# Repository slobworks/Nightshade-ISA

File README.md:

NIGHTSHADE v0.8c2 - Public Domain Cirrus Logic CL-GD542x Based ISA VGA Card

As it says on the package. This card supports a maximum memory size of 1MB or 2MB, depending on the chip you use, using traditional multiple-CAS FPM 256Kx16 SOJ memory. 70ns or faster is recommended.
Created using KiCAD 8.0.

Features:
- Four layer PCB with generous stitching vias for maximum possible signal integrity
- Optional dedicated regulator for analog DAC power for further improved picture quality
- Supports 1MB of memory with CL-GD5424, or 2MB with CL-GD5426/5428/5429
- Compatible with the N-well variants of the CL-GD542x, including the CL-GD5424, GD5426, GD5428 and GD5429
- Uses 29C010-compatible flash memory for reduced cost; has options to select one of four 32K banks within the large 128K flash memory if you wish to try multiple video BIOSes
- Features my own hand-drawn artwork on back of board

Release History:
- 0.8a: Fixed VESA Feature Connector pinout, now conforms to Cirrus datasheet
- 0.8b: Resolved a number of issues related to VGA output quality (no more wavy interference onscreen!), and reduced the parts count a bit. Fewer parts means less $$ spent, and less breathing of solder fumes.
- 0.8b2: Changed LM334SM to the _much_ cheaper LM334M.
- 0.8c: Pretty heavy tweak-up of both layout, ground pours, and placement of 75 ohm termination resistors following feedback from TmEE, Jorge and others. Thanks everyone who spoke up to help.
Also re-added DPAK LF50 regulator for the RAMDAC, and yes, it is optional if you want to pinch pennies on the dollar - just remember to only populate R22 if you're **not** using a regulator. If you're installing the regulator, leave R22 **OPEN**.
- 0.8c1: Changed ROM footprint to an SMD PLCC-32 socket, and had to re-space stuff around it to make it fit. This looks like it ought to work: https://www.digikey.com/en/products/detail/amphenol-cs-fci/69802-132LF/2023294
- 0.8c2: Moved the LDO and related junk to the front of the board to help minimize the potential for damage. Hopefully things don't get too hot, where it is.

Other people's stuff I've used:
- PLCC-32 footprint from KiCAD (SchrodingersGat ?): https://github.com/KiCad/Housings_LCC.pretty/blob/master/PLCC-32_SMD-Socket.kicad_mod

Released into the Public Domain. Use whatever license floats your boat on your own edits.

As you can see I'm a bit of a neophyte when it comes to this GitHub stuff.
Expect this to change as I become more familiar with the platform.

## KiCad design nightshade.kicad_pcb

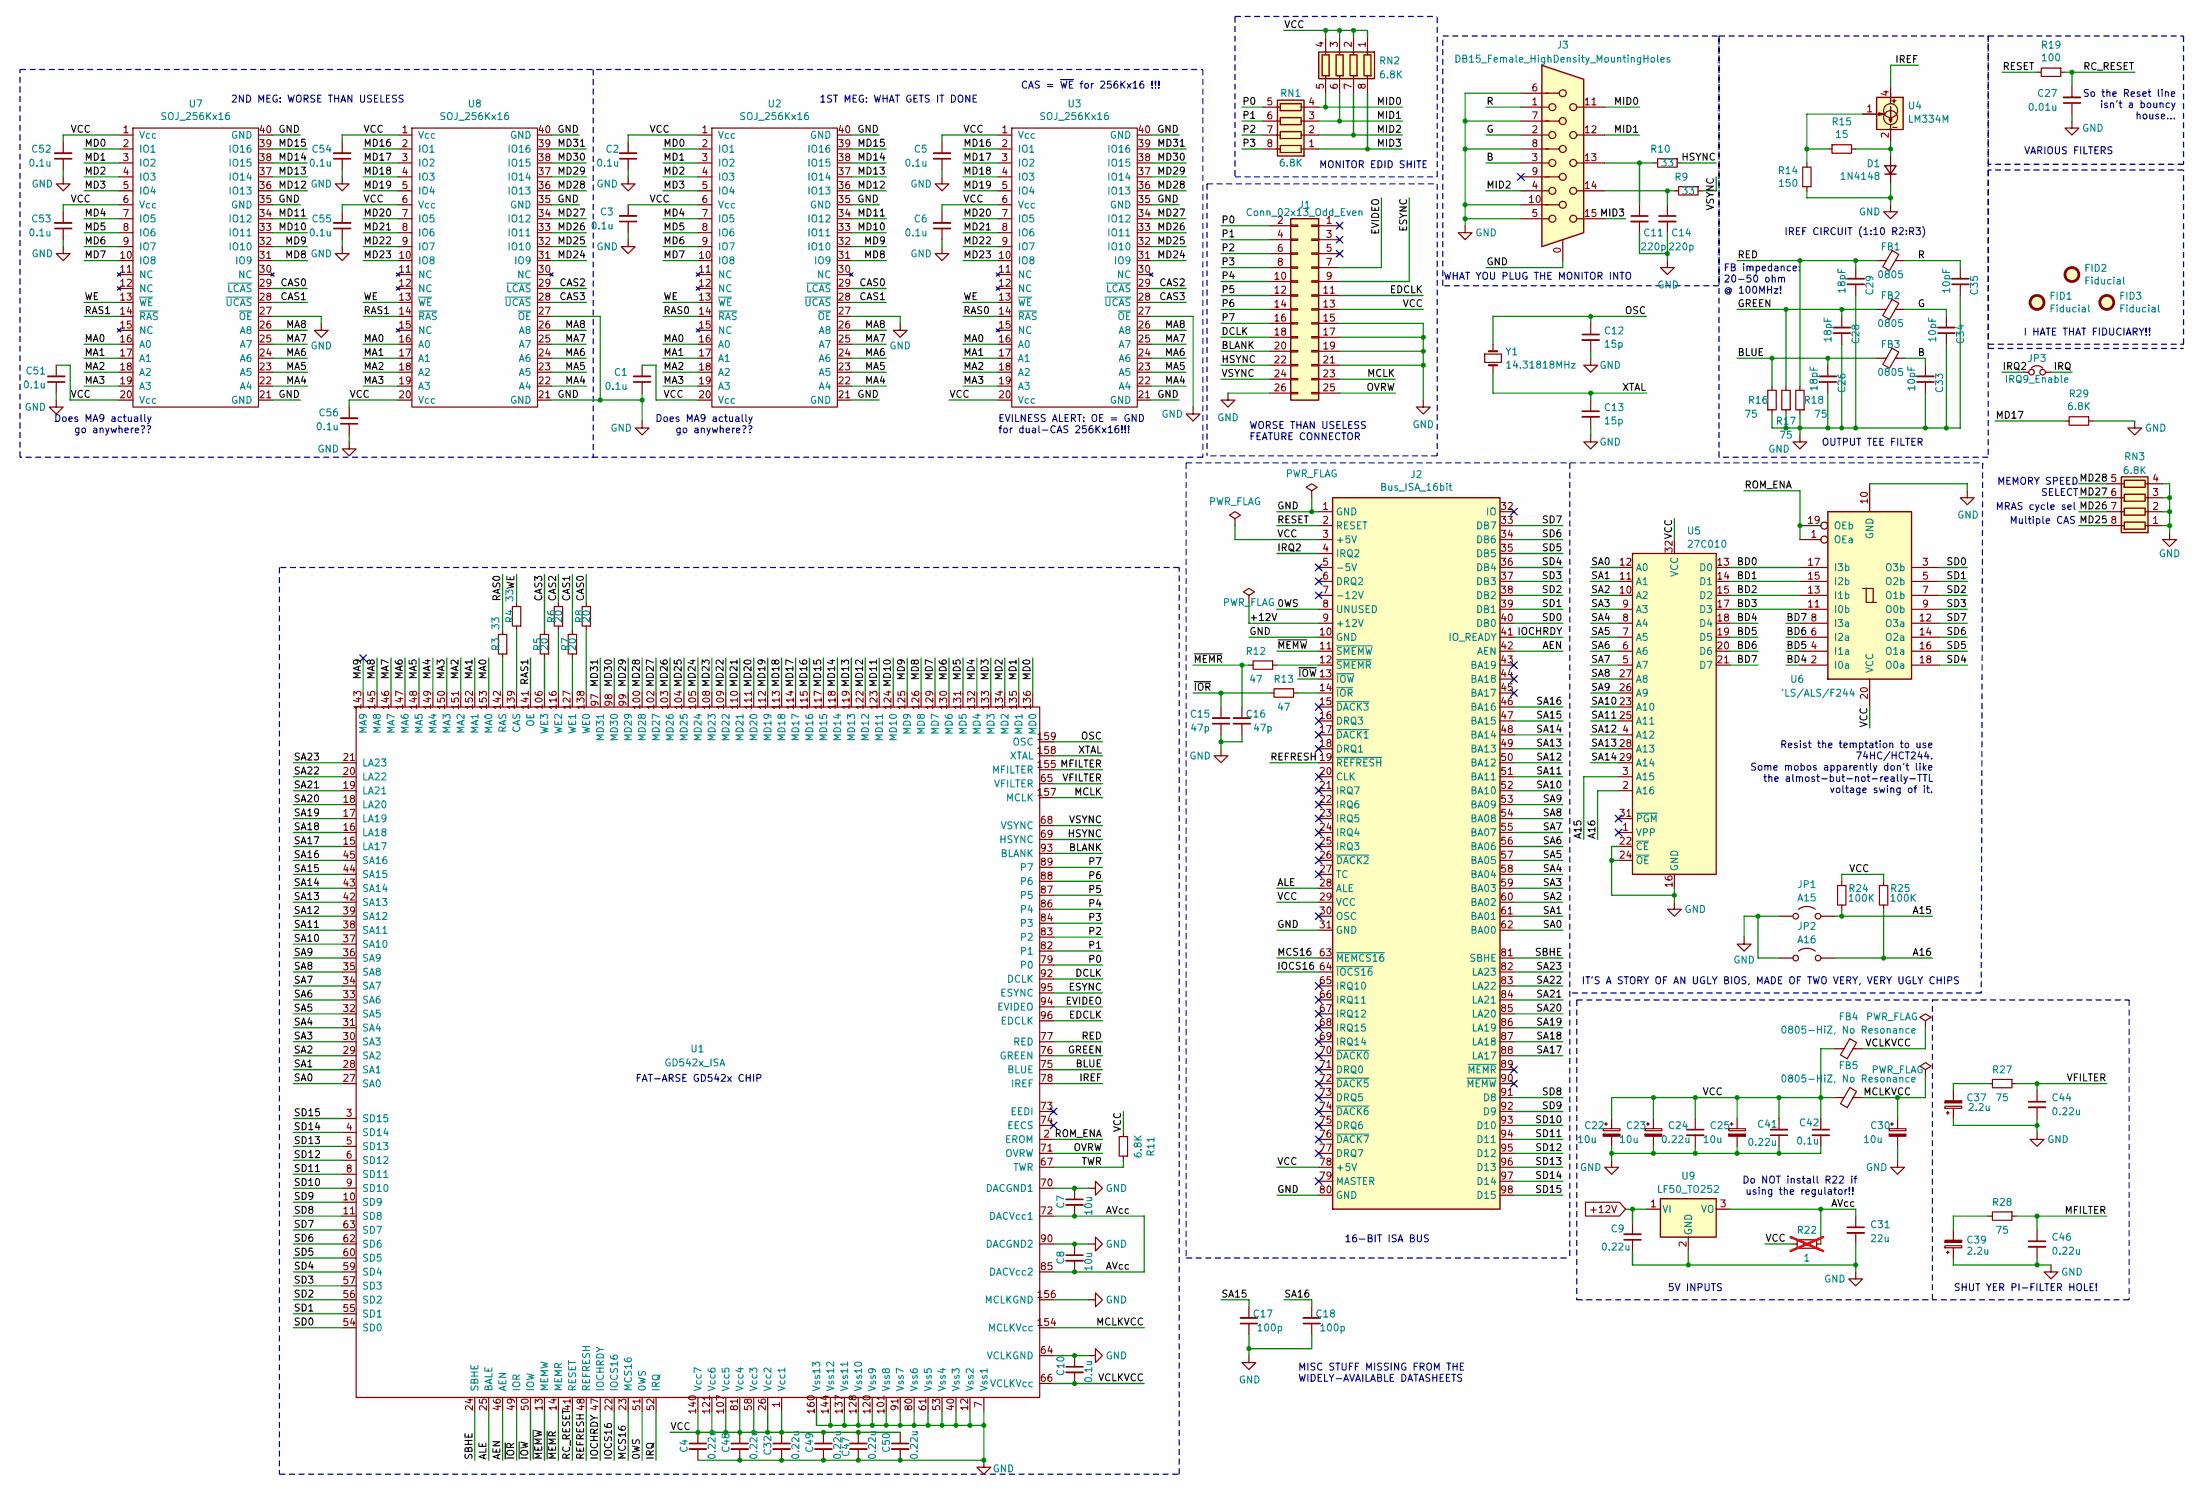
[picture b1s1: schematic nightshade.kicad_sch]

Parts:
C1, C2, C3, C5, C6, C10, C42, C51, C52, C53, C54, C55, C56: 0.1u; C_0805_2012Metric
C4, C9, C24, C32, C41, C44, C46, C47, C48, C49, C50: 0.22u; C_0805_2012Metric
C7, C8, C22, C23, C25, C30: 10u; C_1206_3216Metric
C11, C14: 220p; C_0805_2012Metric
C12, C13: 15p; C_0805_2012Metric
C15, C16: 47p; C_0805_2012Metric
C17, C18: 100p; C_0805_2012Metric
C26, C28, C29: 18pF; C_0805_2012Metric
C27: 0.01u; C_0805_2012Metric
C31: 22u; C_Elec_4x5.8
C33, C34, C35: 10pF; C_0805_2012Metric
C37, C39: 2.2u; C_0805_2012Metric
D1: 1N4148; D_SOD-323_HandSoldering
FB1, FB2, FB3: 0805; L_0805_2012Metric
FB4, FB5: 0805-HiZ, No Resonance; L_0805_2012Metric
FID1, FID2, FID3: Fiducial; Fiducial_1mm_Mask2mm
J1: Conn_02x13_Odd_Even; PinHeader_2x13_P2.54mm_Vertical
J2: Bus_ISA_16bit; BUS_AT
J3: DB15_Female_HighDensity_MountingHoles; DSUB-15-HD
JP1: A15; PinHeader_1x02_P1.27mm_Vertical
JP2: A16; PinHeader_1x02_P1.27mm_Vertical
JP3: IRQ9_Enable; PinHeader_1x02_P2.54mm_Vertical
R3, R4, R9, R10: 33; R_0805_2012Metric
R5, R6, R7, R8: 20; R_0805_2012Metric
R11: 6.8K; R_0603_1608Metric
R12, R13: 47; R_0805_2012Metric
R14: 150; R_0805_2012Metric
R15: 15; R_0805_2012Metric
R16, R17, R18, R27, R28: 75; R_0805_2012Metric
R19: 100; R_0805_2012Metric
R22: 1; R_0805_2012Metric; not fitted
R24, R25: 100K; R_0603_1608Metric
R29: 6.8K; R_0805_2012Metric
RN1, RN2, RN3: 6.8K; R_Array_Convex_4x0603
U1: GD542x_ISA; PQFP-160_28x28mm_P0.65mm
U2, U3, U7, U8: SOJ_256Kx16; SOJ-40_10.16x26.44mm_P1.27mm
U4: LM334M; SOIC-8_3.9x4.9mm_P1.27mm
U5: 27C010; PLCC-32_SMD-Socket
U6: 'LS/ALS/F244; SOIC-20W_7.5x12.8mm_P1.27mm
U9: LF50_TO252; TO-252-2
Y1: 14.31818MHz; Crystal_SMD_5032-2Pin_5.0x3.2mm_HandSoldering

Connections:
+12V: C9.2, J2.9 (+12V), U9.1 (VI)
/0WS: J2.8 (UNUSED), U1.51 (0WS)
/A15: JP1.2 (B), R24.2, U5.3 (A15)
/A16: JP2.2 (B), R25.2, U5.2 (A16)
/AEN: J2.42 (AEN), U1.46 (AEN)
/ALE: J2.28 (ALE), U1.25 (BALE)
/AVcc: C7.2, C8.2, C31.1, R22.1, U1.72 (DACVcc1), U1.85 (DACVcc2), U9.3 (VO)
/B: C33.2, FB3.1, J3.3
/BD0: U5.13 (D0), U6.17 (I3b)
/BD1: U5.14 (D1), U6.15 (I2b)
/BD2: U5.15 (D2), U6.13 (I1b)
/BD3: U5.17 (D3), U6.11 (I0b)
/BD4: U5.18 (D4), U6.2 (I0a)
/BD5: U5.19 (D5), U6.4 (I1a)
/BD6: U5.20 (D6), U6.6 (I2a)
/BD7: U5.21 (D7), U6.8 (I3a)
/BLANK: J1.20, U1.93 (BLANK)
/BLUE: C26.2, FB3.2, R16.2, U1.75 (BLUE)
/CAS0: R8.2, U2.29 (~LCAS), U7.29 (~LCAS)
/CAS1: R7.2, U2.28 (~UCAS), U7.28 (~UCAS)
/CAS2: R6.2, U3.29 (~LCAS), U8.29 (~LCAS)
/CAS3: R5.2, U3.28 (~UCAS), U8.28 (~UCAS)
/DCLK: J1.18, U1.92 (DCLK)
/EDCLK: J1.11, U1.96 (EDCLK)
/ESYNC: J1.9, U1.95 (ESYNC)
/EVIDEO: J1.7, U1.94 (EVIDEO)
/G: C34.2, FB2.1, J3.2
/GREEN: C28.2, FB2.2, R17.2, U1.76 (GREEN)
/HSYNC: J1.22, R10.1, U1.69 (HSYNC)
/IOCHRDY: J2.41 (IO_READY), U1.47 (IOCHRDY)
/IOCS16: J2.64 (~IOCS16), U1.22 (IOCS16)
/IREF: U1.78 (IREF), U4.4
/IRQ: JP3.2, U1.52 (IRQ)
/IRQ2: J2.4 (IRQ2), JP3.1
/MA0: U1.153 (MA0), U2.16 (A0), U3.16 (A0), U7.16 (A0), U8.16 (A0)
/MA1: U1.152 (MA1), U2.17 (A1), U3.17 (A1), U7.17 (A1), U8.17 (A1)
/MA2: U1.151 (MA2), U2.18 (A2), U3.18 (A2), U7.18 (A2), U8.18 (A2)
/MA3: U1.150 (MA3), U2.19 (A3), U3.19 (A3), U7.19 (A3), U8.19 (A3)
/MA4: U1.149 (MA4), U2.22 (A4), U3.22 (A4), U7.22 (A4), U8.22 (A4)
/MA5: U1.148 (MA5), U2.23 (A5), U3.23 (A5), U7.23 (A5), U8.23 (A5)
/MA6: U1.147 (MA6), U2.24 (A6), U3.24 (A6), U7.24 (A6), U8.24 (A6)
/MA7: U1.146 (MA7), U2.25 (A7), U3.25 (A7), U7.25 (A7), U8.25 (A7)
/MA8: U1.145 (MA8), U2.26 (A8), U3.26 (A8), U7.26 (A8), U8.26 (A8)
/MA9: U1.143 (MA9)
/MCLK: J1.23, U1.157 (MCLK)
/MCLKVCC: C30.1, FB5.2, U1.154 (MCLKVcc)
/MCS16: J2.63 (~MEMCS16), U1.23 (MCS16)
/MD0: U1.136 (MD0), U2.2 (IO1), U7.2 (IO1)
/MD1: U1.135 (MD1), U2.3 (IO2), U7.3 (IO2)
/MD2: U1.134 (MD2), U2.4 (IO3), U7.4 (IO3)
/MD3: U1.133 (MD3), U2.5 (IO4), U7.5 (IO4)
/MD4: U1.132 (MD4), U2.7 (IO5), U7.7 (IO5)
/MD5: U1.131 (MD5), U2.8 (IO6), U7.8 (IO6)
/MD6: U1.130 (MD6), U2.9 (IO7), U7.9 (IO7)
/MD7: U1.129 (MD7), U2.10 (IO8), U7.10 (IO8)
/MD8: U1.126 (MD8), U2.31 (IO9), U7.31 (IO9)
/MD9: U1.125 (MD9), U2.32 (IO10), U7.32 (IO10)
/MD10: U1.124 (MD10), U2.33 (IO11), U7.33 (IO11)
/MD11: U1.123 (MD11), U2.34 (IO12), U7.34 (IO12)
/MD12: U1.122 (MD12), U2.36 (IO13), U7.36 (IO13)
/MD13: U1.119 (MD13), U2.37 (IO14), U7.37 (IO14)
/MD14: U1.118 (MD14), U2.38 (IO15), U7.38 (IO15)
/MD15: U1.117 (MD15), U2.39 (IO16), U7.39 (IO16)
/MD16: U1.115 (MD16), U3.2 (IO1), U8.2 (IO1)
/MD17: R29.2, U1.114 (MD17), U3.3 (IO2), U8.3 (IO2)
/MD18: U1.113 (MD18), U3.4 (IO3), U8.4 (IO3)
/MD19: U1.112 (MD19), U3.5 (IO4), U8.5 (IO4)
/MD20: U1.111 (MD20), U3.7 (IO5), U8.7 (IO5)
/MD21: U1.110 (MD21), U3.8 (IO6), U8.8 (IO6)
/MD22: U1.109 (MD22), U3.9 (IO7), U8.9 (IO7)
/MD23: U1.108 (MD23), U3.10 (IO8), U8.10 (IO8)
/MD24: U1.105 (MD24), U3.31 (IO9), U8.31 (IO9)
/MD25: RN3.8 (R1.2), U1.104 (MD25), U3.32 (IO10), U8.32 (IO10)
/MD26: RN3.7 (R2.2), U1.103 (MD26), U3.33 (IO11), U8.33 (IO11)
/MD27: RN3.6 (R3.2), U1.102 (MD27), U3.34 (IO12), U8.34 (IO12)
/MD28: RN3.5 (R4.2), U1.100 (MD28), U3.36 (IO13), U8.36 (IO13)
/MD29: U1.99 (MD29), U3.37 (IO14), U8.37 (IO14)
/MD30: U1.98 (MD30), U3.38 (IO15), U8.38 (IO15)
/MD31: U1.97 (MD31), U3.39 (IO16), U8.39 (IO16)
/MFILTER: C46.1, R28.1, U1.155 (MFILTER)
/MID0: J3.11, RN1.4 (R4.1), RN2.5 (R4.2)
/MID1: J3.12, RN1.3 (R3.1), RN2.6 (R3.2)
/MID2: J3.4, RN1.2 (R2.1), RN2.7 (R2.2)
/MID3: J3.15, RN1.1 (R1.1), RN2.8 (R1.2)
/OSC: C12.1, U1.159 (OSC), Y1.1
/OVRW: J1.25, U1.71 (OVRW)
/P0: J1.2, RN1.5 (R4.2), U1.79 (P0)
/P1: J1.4, RN1.6 (R3.2), U1.82 (P1)
/P2: J1.6, RN1.7 (R2.2), U1.83 (P2)
/P3: J1.8, RN1.8 (R1.2), U1.84 (P3)
/P4: J1.10, U1.86 (P4)
/P5: J1.12, U1.87 (P5)
/P6: J1.14, U1.88 (P6)
/P7: J1.16, U1.89 (P7)
/R: C35.2, FB1.1, J3.1
/RAS0: R3.2, U2.14 (~RAS), U3.14 (~RAS)
/RAS1: U1.141 (OE), U7.14 (~RAS), U8.14 (~RAS)
/RC_RESET: C27.2, R19.1, U1.41 (RESET)
/RED: C29.2, FB1.2, R18.2, U1.77 (RED)
/REFRESH: J2.19 (~REFRESH), U1.48 (REFRESH)
/RESET: J2.2 (RESET), R19.2
/ROM_ENA: U1.2 (EROM), U6.1 (OEa), U6.19 (OEb)
/SA0: J2.62 (BA00), U1.27 (SA0), U5.12 (A0)
/SA1: J2.61 (BA01), U1.28 (SA1), U5.11 (A1)
/SA2: J2.60 (BA02), U1.29 (SA2), U5.10 (A2)
/SA3: J2.59 (BA03), U1.30 (SA3), U5.9 (A3)
/SA4: J2.58 (BA04), U1.31 (SA4), U5.8 (A4)
/SA5: J2.57 (BA05), U1.32 (SA5), U5.7 (A5)
/SA6: J2.56 (BA06), U1.33 (SA6), U5.6 (A6)
/SA7: J2.55 (BA07), U1.34 (SA7), U5.5 (A7)
/SA8: J2.54 (BA08), U1.35 (SA8), U5.27 (A8)
/SA9: J2.53 (BA09), U1.36 (SA9), U5.26 (A9)
/SA10: J2.52 (BA10), U1.37 (SA10), U5.23 (A10)
/SA11: J2.51 (BA11), U1.38 (SA11), U5.25 (A11)
/SA12: J2.50 (BA12), U1.39 (SA12), U5.4 (A12)
/SA13: J2.49 (BA13), U1.42 (SA13), U5.28 (A13)
/SA14: J2.48 (BA14), U1.43 (SA14), U5.29 (A14)
/SA15: C17.2, J2.47 (BA15), U1.44 (SA15)
/SA16: C18.2, J2.46 (BA16), U1.45 (SA16)
/SA17: J2.88 (LA17), U1.15 (LA17)
/SA18: J2.87 (LA18), U1.16 (LA18)
/SA19: J2.86 (LA19), U1.17 (LA19)
/SA20: J2.85 (LA20), U1.18 (LA20)
/SA21: J2.84 (LA21), U1.19 (LA21)
/SA22: J2.83 (LA22), U1.20 (LA22)
/SA23: J2.82 (LA23), U1.21 (LA23)
/SBHE: J2.81 (SBHE), U1.24 (SBHE)
/SD0: J2.40 (DB0), U1.54 (SD0), U6.3 (O3b)
/SD1: J2.39 (DB1), U1.55 (SD1), U6.5 (O2b)
/SD2: J2.38 (DB2), U1.56 (SD2), U6.7 (O1b)
/SD3: J2.37 (DB3), U1.57 (SD3), U6.9 (O0b)
/SD4: J2.36 (DB4), U1.59 (SD4), U6.18 (O0a)
/SD5: J2.35 (DB5), U1.60 (SD5), U6.16 (O1a)
/SD6: J2.34 (DB6), U1.62 (SD6), U6.14 (O2a)
/SD7: J2.33 (DB7), U1.63 (SD7), U6.12 (O3a)
/SD8: J2.91 (D8), U1.11 (SD8)
/SD9: J2.92 (D9), U1.10 (SD9)
/SD10: J2.93 (D10), U1.9 (SD10)
/SD11: J2.94 (D11), U1.8 (SD11)
/SD12: J2.95 (D12), U1.6 (SD12)
/SD13: J2.96 (D13), U1.5 (SD13)
/SD14: J2.97 (D14), U1.4 (SD14)
/SD15: J2.98 (D15), U1.3 (SD15)
/TWR: R11.1, U1.67 (TWR)
/VCC: C1.2, C2.2, C3.2, C4.1, C5.2, C6.2, C22.1, C23.1, C24.1, C25.1, C32.1, C41.2, C42.1, C47.1, C48.1, C49.1, C50.1, C51.2, C52.2, C53.2, C54.2, C55.2, C56.2, FB4.1, FB5.1, J1.13, J2.3 (+5V), J2.29 (VCC), J2.78 (+5V), R11.2, R22.2, R24.1, R25.1, RN2.1 (R1.1), RN2.2 (R2.1), RN2.3 (R3.1), RN2.4 (R4.1), U1.1 (Vcc1), U1.26 (Vcc2), U1.58 (Vcc3), U1.81 (Vcc4), U1.107 (Vcc5), U1.121 (Vcc6), U1.140 (Vcc7), U2.1 (Vcc), U2.6 (Vcc), U2.20 (Vcc), U3.1 (Vcc), U3.6 (Vcc), U3.20 (Vcc), U5.32 (VCC), U6.20 (VCC), U7.1 (Vcc), U7.6 (Vcc), U7.20 (Vcc), U8.1 (Vcc), U8.6 (Vcc), U8.20 (Vcc)
/VCLKVCC: C10.2, FB4.2, U1.66 (VCLKVcc)
/VFILTER: C44.1, R27.1, U1.65 (VFILTER)
/VSYNC: J1.24, R9.1, U1.68 (VSYNC)
/WE: R4.2, U2.13 (~WE), U3.13 (~WE), U7.13 (~WE), U8.13 (~WE)
/XTAL: C13.1, U1.158 (XTAL), Y1.2
/~IOR: C15.2, R13.2, U1.49 (IOR)
/~IOW: J2.13 (~IOW), U1.50 (IOW)
/~MEMR: C16.2, R12.2, U1.14 (MEMR)
/~MEMW: J2.11 (~SMEMW), U1.13 (MEMW)
GND: C1.1, C2.1, C3.1, C4.2, C5.1, C6.1, C7.1, C8.1, C9.1, C10.1, C11.2, C12.2, C13.2, C14.2, C15.1, C16.1, C17.1, C18.1, C22.2, C23.2, C24.2, C25.2, C26.1, C27.1, C28.1, C29.1, C30.2, C31.2, C32.2, C33.1, C34.1, C35.1, C37.1, C39.1, C41.1, C42.2, C44.2, C46.2, C47.2, C48.2, C49.2, C50.2, C51.1, C52.1, C53.1, C54.1, C55.1, C56.1, D1.1 (K), J1.15, J1.17, J1.19, J1.21, J1.26, J2.1 (GND), J2.10 (GND), J2.31 (GND), J2.80 (GND), J3.0, J3.5, J3.6, J3.7, J3.8, J3.10, JP1.1 (A), JP2.1 (A), R14.1, R16.1, R17.1, R18.1, R29.1, RN3.1 (R1.1), RN3.2 (R2.1), RN3.3 (R3.1), RN3.4 (R4.1), U1.7 (Vss1), U1.12 (Vss2), U1.40 (Vss3), U1.53 (Vss4), U1.61 (Vss5), U1.64 (VCLKGND), U1.70 (DACGND1), U1.80 (Vss6), U1.90 (DACGND2), U1.91 (Vss7), U1.101 (Vss8), U1.120 (Vss9), U1.128 (Vss10), U1.137 (Vss11), U1.144 (Vss12), U1.156 (MCLKGND), U1.160 (Vss13), U2.21 (GND), U2.27 (~OE), U2.35 (GND), U2.40 (GND), U3.21 (GND), U3.27 (~OE), U3.35 (GND), U3.40 (GND), U5.16 (GND), U5.22 (~CE), U5.24 (~OE), U6.10 (GND), U7.21 (GND), U7.27 (~OE), U7.35 (GND), U7.40 (GND), U8.21 (GND), U8.27 (~OE), U8.35 (GND), U8.40 (GND), U9.2 (GND)
unnamed: C11.1, J3.13, R10.2
unnamed: C14.1, J3.14, R9.2
unnamed: C37.2, R27.2
unnamed: C39.2, R28.2
unnamed: D1.2 (A), R15.2, U4.2, U4.3, U4.6, U4.7
unnamed: J2.14 (~IOR), R13.1
unnamed: J2.12 (~SMEMR), R12.1
unnamed: R14.2, R15.1, U4.1
unnamed: R4.1, U1.139 (CAS)
unnamed: R3.1, U1.142 (RAS)
unnamed: R8.1, U1.138 (WE0)
unnamed: R7.1, U1.127 (WE1)
unnamed: R6.1, U1.116 (WE2)
unnamed: R5.1, U1.106 (WE3)

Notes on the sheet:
Resist the temptation to use 74HC/HCT244. Some mobos apparently don't like the almost-but-not-really-TTL voltage swing of it.
16-BIT ISA BUS
IT'S A STORY OF AN UGLY BIOS, MADE OF TWO VERY, VERY UGLY CHIPS
Multiple CAS
Does MA9 actually go anywhere??
So the Reset line isn't a bouncy house...
2ND MEG: WORSE THAN USELESS
VARIOUS FILTERS
SHUT YER PI-FILTER HOLE!
MONITOR EDID SHITE
IREF CIRCUIT (1:10 R2:R3)
CAS = ~{WE} for 256Kx16 !!!
Do NOT install R22 if using the regulator!!
FAT-ARSE GD542x CHIP
1ST MEG: WHAT GETS IT DONE
MISC STUFF MISSING FROM THE WIDELY-AVAILABLE DATASHEETS
MEMORY SPEED SELECT
5V INPUTS
WHAT YOU PLUG THE MONITOR INTO
FB impedance: 20-50 ohm @ 100MHz!
WORSE THAN USELESS FEATURE CONNECTOR
I HATE THAT FIDUCIARY!!
MRAS cycle sel
EVILNESS ALERT: OE = GND for dual-CAS 256Kx16!!!
OUTPUT TEE FILTER

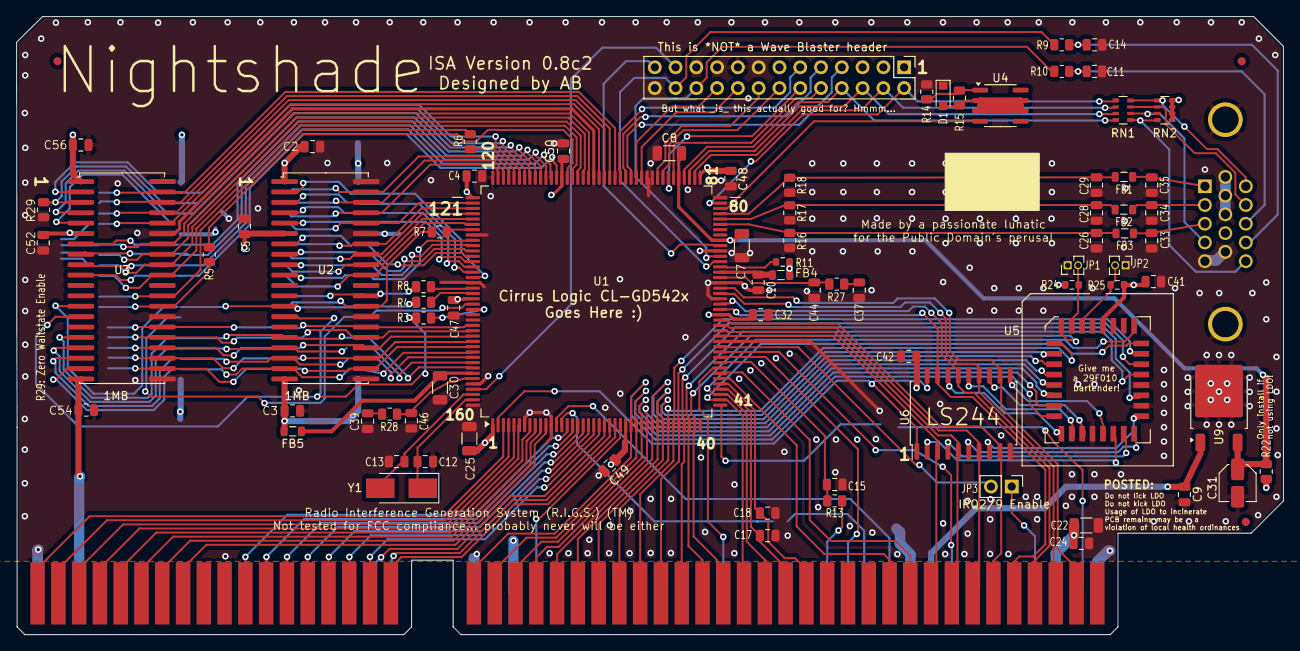
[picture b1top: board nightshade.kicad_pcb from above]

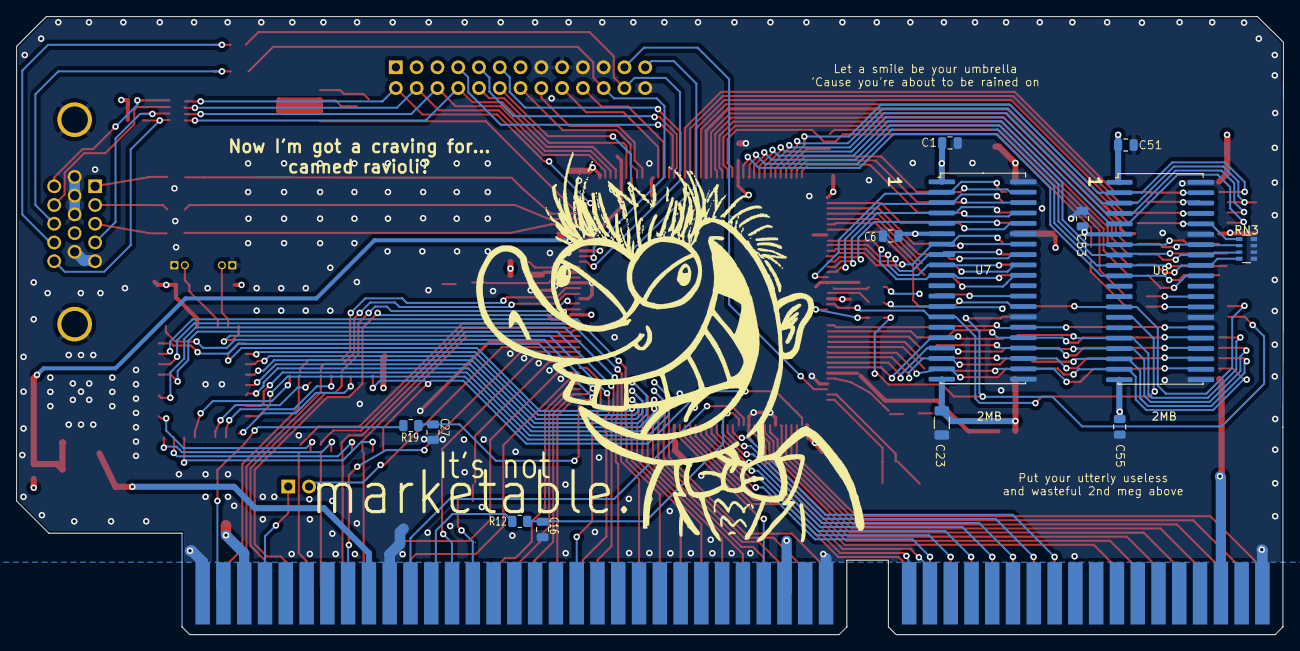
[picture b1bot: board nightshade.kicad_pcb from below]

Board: 4 copper layers, 154.9 x 75.5 mm, 100 parts (14 on the bottom side), 168 nets.

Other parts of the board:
G1: LOGO; ugly

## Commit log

2024-11-25 Add files via upload
    Nightshade: Public Domain CL-GD542x 1MB ISA VGA card
2024-12-14 Add files via upload
    Updated to Version 0.8
2024-12-14 Update README.md
    Ooh, pictures!
2024-12-24 Update README.md
    Whoopsadoodle, realized that the VFC connector is busted
2024-12-24 Add files via upload
    Uploaded version 0.8a, which fixes among other things the VFC connector pinout.
2024-12-24 Add files via upload
    Added CSV BOM file
2024-12-24 Add files via upload
    quick fixes
2024-12-24 Add files via upload
    0.8a is finalized! Merry Christmas!
2024-12-24 Update README.md
    Updated pictures. Again.
2024-12-26 Add files via upload
    Updated to version 0.8b. Merry Christmas!
2024-12-26 Update README.md
    Updated to Version 0.8b
2024-12-29 Add files via upload
    Updated to 0.8b2
2025-01-02 Add files via upload
    Updated to version 0.8c.
2025-01-02 Update README.md
    Updated to Version 0.8c.
2025-01-02 Add files via upload
    updated to 0.8c1.
2025-01-02 Add files via upload
    Updated to Version 0.8c2.

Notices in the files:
nightshade.kicad_pcb:
for the Public Domain's perusal
